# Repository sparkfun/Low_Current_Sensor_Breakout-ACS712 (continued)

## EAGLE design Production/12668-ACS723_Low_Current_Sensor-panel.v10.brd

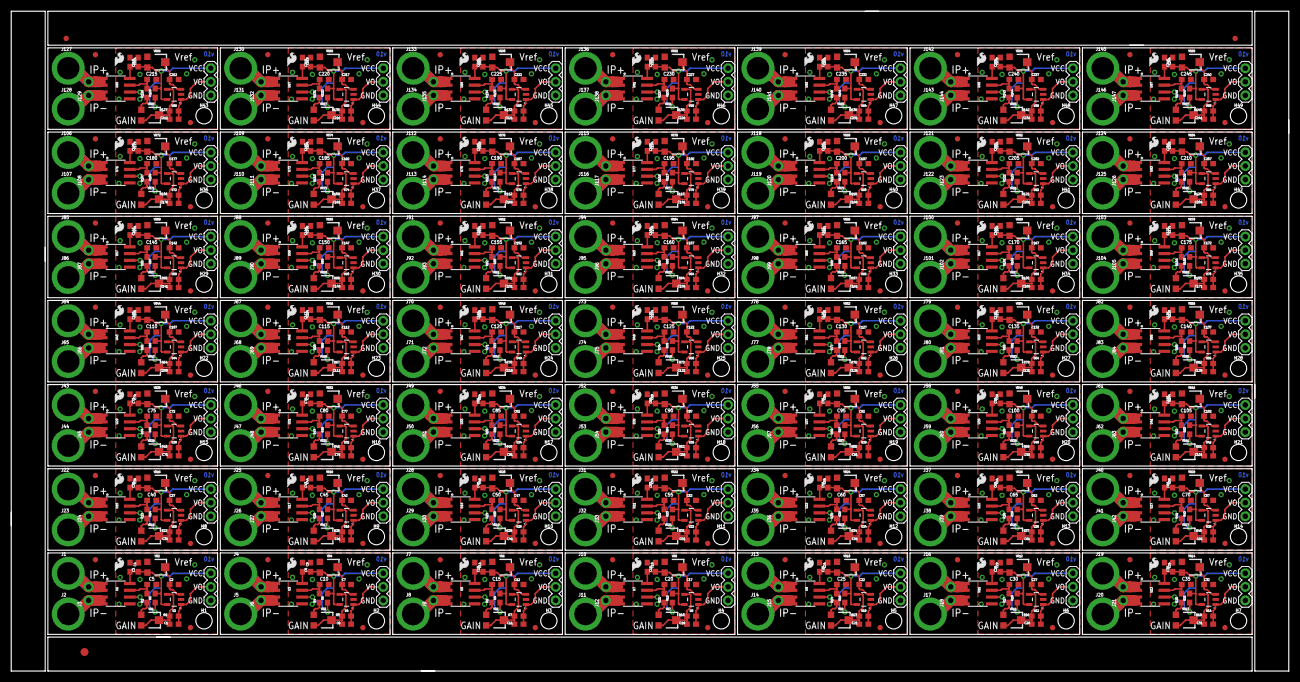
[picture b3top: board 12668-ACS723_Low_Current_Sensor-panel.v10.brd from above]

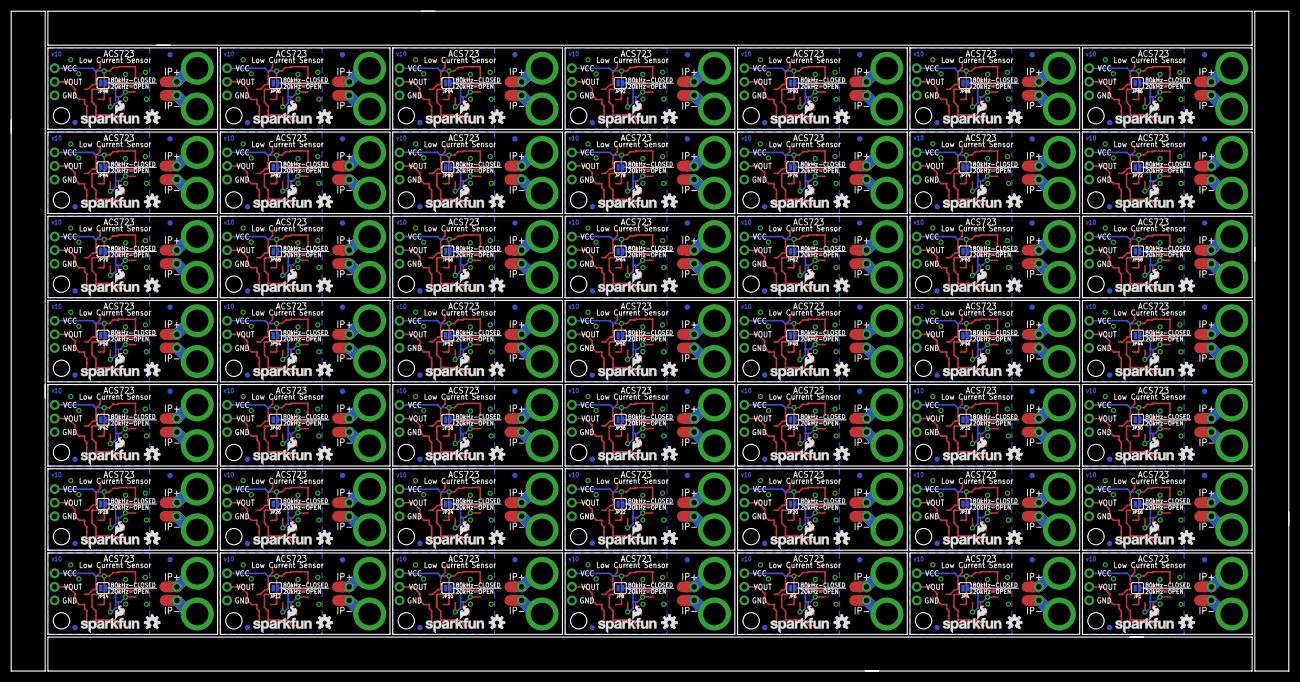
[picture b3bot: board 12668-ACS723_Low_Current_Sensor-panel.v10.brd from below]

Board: 2 copper layers, 239.0 x 123.4 mm, 1228 parts (245 on the bottom side), 490 nets.

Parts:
C1, C6, C11, C16, C21, C26, C31, C36, C41, C46, C51, C56, C61, C66, C71, C76, C81, C86, C91, C96, C101, C106, C111, C116, C121, C126, C131, C136, C141, C146, C151, C156, C161, C166, C171, C176, C181, C186, C191, C196, C201, C206, C211, C216, C221, C226, C231, C236, C241: 100pF; 0603
C2, C3, C4, C7, C8, C9, C12, C13, C14, C17, C18, C19, C22, C23, C24, C27, C28, C29, C32, C33, C34, C37, C38, C39, C42, C43, C44, C47, C48, C49, C52, C53, C54, C57, C58, C59, C62, C63, C64, C67, C68, C69, C72, C73, C74, C77, C78, C79, C82, C83, C84, C87, C88, C89, C92, C93, C94, C97, C98, C99, C102, C103, C104, C107, C108, C109, C112, C113, C114, C117, C118, C119, C122, C123, C124, C127, C128, C129, C132, C133, C134, C137, C138, C139, C142, C143, C144, C147, C148, C149, C152, C153, C154, C157, C158, C159, C162, C163, C164, C167, C168, C169, C172, C173, C174, C177, C178, C179, C182, C183, C184, C187, C188, C189, C192, C193, C194, C197, C198, C199, C202, C203, C204, C207, C208, C209, C212, C213, C214, C217, C218, C219, C222, C223, C224, C227, C228, C229, C232, C233, C234, C237, C238, C239, C242, C243, C244: 0.1uF; 0603
C5, C10, C15, C20, C25, C30, C35, C40, C45, C50, C55, C60, C65, C70, C75, C80, C85, C90, C95, C100, C105, C110, C115, C120, C125, C130, C135, C140, C145, C150, C155, C160, C165, C170, C175, C180, C185, C190, C195, C200, C205, C210, C215, C220, C225, C230, C235, C240, C245: 1nF; 0603
E$1: FIDUCIAL-1.5X3
E$7, E$8: FIDUCIAL-1X2
FD1, FD2, FD3, FD4, FD5, FD6, FD7, FD8, FD9, FD10, FD11, FD12, FD13, FD14, FD15, FD16, FD17, FD18, FD19, FD20, FD21, FD22, FD23, FD24, FD25, FD26, FD27, FD28, FD29, FD30, FD31, FD32, FD33, FD34, FD35, FD36, FD37, FD38, FD39, FD40, FD41, FD42, FD43, FD44, FD45, FD46, FD47, FD48, FD49, FD50, FD51, FD52, FD53, FD54, FD55, FD56, FD57, FD58, FD59, FD60, FD61, FD62, FD63, FD64, FD65, FD66, FD67, FD68, FD69, FD70, FD71, FD72, FD73, FD74, FD75, FD76, FD77, FD78, FD79, FD80, FD81, FD82, FD83, FD84, FD85, FD86, FD87, FD88, FD89, FD90, FD91, FD92, FD93, FD94, FD95, FD96, FD97, FD98, FD99, FD100, FD101, FD102, FD103, FD104, FD105, FD106, FD107, FD108, FD109, FD110, FD111, FD112, FD113, FD114, FD115, FD116, FD117, FD118, FD119, FD120, FD121, FD122, FD123, FD124, FD125, FD126, FD127, FD128, FD129, FD130, FD131, FD132, FD133, FD134, FD135, FD136, FD137, FD138, FD139, FD140, FD141, FD142, FD143, FD144, FD145, FD146, FD147, FD148, FD149, FD150, FD151, FD152, FD153, FD154, FD155, FD156, FD157, FD158, FD159, FD160, FD161, FD162, FD163, FD164, FD165, FD166, FD167, FD168, FD169, FD170, FD171, FD172, FD173, FD174, FD175, FD176, FD177, FD178, FD179, FD180, FD181, FD182, FD183, FD184, FD185, FD186, FD187, FD188, FD189, FD190, FD191, FD192, FD193, FD194, FD195, FD196: FIDUCIAL1X2; FIDUCIAL-1X2
H1, H2, H3, H4, H5, H6, H7, H8, H9, H10, H11, H12, H13, H14, H15, H16, H17, H18, H19, H20, H21, H22, H23, H24, H25, H26, H27, H28, H29, H30, H31, H32, H33, H34, H35, H36, H37, H38, H39, H40, H41, H42, H43, H44, H45, H46, H47, H48, H49: STAND-OFFTIGHT; STAND-OFF-TIGHT
J1, J2, J4, J5, J7, J8, J10, J11, J13, J14, J16, J17, J19, J20, J22, J23, J25, J26, J28, J29, J31, J32, J34, J35, J37, J38, J40, J41, J43, J44, J46, J47, J49, J50, J52, J53, J55, J56, J58, J59, J61, J62, J64, J65, J67, J68, J70, J71, J73, J74, J76, J77, J79, J80, J82, J83, J85, J86, J88, J89, J91, J92, J94, J95, J97, J98, J100, J101, J103, J104, J106, J107, J109, J110, J112, J113, J115, J116, J118, J119, J121, J122, J124, J125, J127, J128, J130, J131, J133, J134, J136, J137, J139, J140, J142, J143, J145, J146: SMTSO-256-ET-0.165DIA
J3, J6, J9, J12, J15, J18, J21, J24, J27, J30, J33, J36, J39, J42, J45, J48, J51, J54, J57, J60, J63, J66, J69, J72, J75, J78, J81, J84, J87, J90, J93, J96, J99, J102, J105, J108, J111, J114, J117, J120, J123, J126, J129, J132, J135, J138, J141, J144, J147: 1X02_NO_SILK
JP1, JP4, JP6, JP8, JP10, JP12, JP14, JP16, JP18, JP20, JP22, JP24, JP26, JP28, JP30, JP32, JP34, JP36, JP38, JP40, JP42, JP44, JP46, JP48, JP50, JP52, JP54, JP56, JP58, JP60, JP62, JP64, JP66, JP68, JP70, JP72, JP74, JP76, JP78, JP80, JP82, JP84, JP86, JP88, JP90, JP92, JP94, JP96, JP98: JUMPER-SMT_2_NO_SILK; SMT-JUMPER_2_NO_SILK
JP2, JP3, JP5, JP7, JP9, JP11, JP13, JP15, JP17, JP19, JP21, JP23, JP25, JP27, JP29, JP31, JP33, JP35, JP37, JP39, JP41, JP43, JP45, JP47, JP49, JP51, JP53, JP55, JP57, JP59, JP61, JP63, JP65, JP67, JP69, JP71, JP73, JP75, JP77, JP79, JP81, JP83, JP85, JP87, JP89, JP91, JP93, JP95, JP97: 1X03
LOGO1, LOGO4, LOGO7, LOGO10, LOGO13, LOGO16, LOGO19, LOGO22, LOGO25, LOGO28, LOGO31, LOGO34, LOGO37, LOGO40, LOGO43, LOGO46, LOGO49, LOGO52, LOGO55, LOGO58, LOGO61, LOGO64, LOGO67, LOGO70, LOGO73, LOGO76, LOGO79, LOGO82, LOGO85, LOGO88, LOGO91, LOGO94, LOGO97, LOGO100, LOGO103, LOGO106, LOGO109, LOGO112, LOGO115, LOGO118, LOGO121, LOGO124, LOGO127, LOGO130, LOGO133, LOGO136, LOGO139, LOGO142, LOGO145: SFE_LOGO_NAME_FLAME.1_INCH; SFE_LOGO_NAME_FLAME_.1
LOGO2, LOGO5, LOGO8, LOGO11, LOGO14, LOGO17, LOGO20, LOGO23, LOGO26, LOGO29, LOGO32, LOGO35, LOGO38, LOGO41, LOGO44, LOGO47, LOGO50, LOGO53, LOGO56, LOGO59, LOGO62, LOGO65, LOGO68, LOGO71, LOGO74, LOGO77, LOGO80, LOGO83, LOGO86, LOGO89, LOGO92, LOGO95, LOGO98, LOGO101, LOGO104, LOGO107, LOGO110, LOGO113, LOGO116, LOGO119, LOGO122, LOGO125, LOGO128, LOGO131, LOGO134, LOGO137, LOGO140, LOGO143, LOGO146: OSHW-LOGOS; OSHW-LOGO-S
LOGO3, LOGO6, LOGO9, LOGO12, LOGO15, LOGO18, LOGO21, LOGO24, LOGO27, LOGO30, LOGO33, LOGO36, LOGO39, LOGO42, LOGO45, LOGO48, LOGO51, LOGO54, LOGO57, LOGO60, LOGO63, LOGO66, LOGO69, LOGO72, LOGO75, LOGO78, LOGO81, LOGO84, LOGO87, LOGO90, LOGO93, LOGO96, LOGO99, LOGO102, LOGO105, LOGO108, LOGO111, LOGO114, LOGO117, LOGO120, LOGO123, LOGO126, LOGO129, LOGO132, LOGO135, LOGO138, LOGO141, LOGO144, LOGO147: SFE_LOGO_FLAME.1_INCH; SFE_LOGO_FLAME_.1
R1, R3, R7, R10, R13, R16, R19, R22, R25, R28, R31, R34, R37, R40, R43, R46, R49, R52, R55, R58, R61, R64, R67, R70, R73, R76, R79, R82, R85, R88, R91, R94, R97, R100, R103, R106, R109, R112, R115, R118, R121, R124, R127, R130, R133, R136, R139, R142, R145: 22k; 0603
R2, R4, R8, R11, R14, R17, R20, R23, R26, R29, R32, R35, R38, R41, R44, R47, R50, R53, R56, R59, R62, R65, R68, R71, R74, R77, R80, R83, R86, R89, R92, R95, R98, R101, R104, R107, R110, R113, R116, R119, R122, R125, R128, R131, R134, R137, R140, R143, R146: 1k; 0603
R5, R6, R9, R12, R15, R18, R21, R24, R27, R30, R33, R36, R39, R42, R45, R48, R51, R54, R57, R60, R63, R66, R69, R72, R75, R78, R81, R84, R87, R90, R93, R96, R99, R102, R105, R108, R111, R114, R117, R120, R123, R126, R129, R132, R135, R138, R141, R144, R147: 4.7k; 0603
U1, U3, U5, U7, U9, U11, U13, U15, U17, U19, U21, U23, U25, U27, U29, U31, U33, U35, U37, U39, U41, U43, U45, U47, U49, U51, U53, U55, U57, U59, U61, U63, U65, U67, U69, U71, U73, U75, U77, U79, U81, U83, U85, U87, U89, U91, U93, U95, U97: ACS723; SO08
U2, U4, U6, U8, U10, U12, U14, U16, U18, U20, U22, U24, U26, U28, U30, U32, U34, U36, U38, U40, U42, U44, U46, U48, U50, U52, U54, U56, U58, U60, U62, U64, U66, U68, U70, U72, U74, U76, U78, U80, U82, U84, U86, U88, U90, U92, U94, U96, U98: OPA344; SOT23-5
VR1, VR2, VR3, VR4, VR5, VR6, VR7, VR8, VR9, VR10, VR11, VR12, VR13, VR14, VR15, VR16, VR17, VR18, VR19, VR20, VR21, VR22, VR23, VR24, VR25, VR26, VR27, VR28, VR29, VR30, VR31, VR32, VR33, VR34, VR35, VR36, VR37, VR38, VR39, VR40, VR41, VR42, VR43, VR44, VR45, VR46, VR47, VR48, VR49, VR50, VR51, VR52, VR53, VR54, VR55, VR56, VR57, VR58, VR59, VR60, VR61, VR62, VR63, VR64, VR65, VR66, VR67, VR68, VR69, VR70, VR71, VR72, VR73, VR74, VR75, VR76, VR77, VR78, VR79, VR80, VR81, VR82, VR83, VR84, VR85, VR86, VR87, VR88, VR89, VR90, VR91, VR92, VR93, VR94, VR95, VR96, VR97, VR98: 10k; TRIMPOT-SMD-TC33X

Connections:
5V: C3.1, C4.2, JP3.1, R5.2, U1.8, U2.5, VR2.3
5V1: C8.1, C9.2, JP2.1, R6.2, U3.8, U4.5, VR4.3
5V2: C13.1, C14.2, JP5.1, R9.2, U5.8, U6.5, VR6.3
5V3: C18.1, C19.2, JP7.1, R12.2, U7.8, U8.5, VR8.3
5V4: C23.1, C24.2, JP9.1, R15.2, U9.8, U10.5, VR10.3
5V5: C28.1, C29.2, JP11.1, R18.2, U11.8, U12.5, VR12.3
5V6: C33.1, C34.2, JP13.1, R21.2, U13.8, U14.5, VR14.3
5V7: C38.1, C39.2, JP15.1, R24.2, U15.8, U16.5, VR16.3
5V8: C43.1, C44.2, JP17.1, R27.2, U17.8, U18.5, VR18.3
5V9: C48.1, C49.2, JP19.1, R30.2, U19.8, U20.5, VR20.3
5V10: C53.1, C54.2, JP21.1, R33.2, U21.8, U22.5, VR22.3
5V11: C58.1, C59.2, JP23.1, R36.2, U23.8, U24.5, VR24.3
5V12: C63.1, C64.2, JP25.1, R39.2, U25.8, U26.5, VR26.3
5V13: C68.1, C69.2, JP27.1, R42.2, U27.8, U28.5, VR28.3
5V14: C73.1, C74.2, JP29.1, R45.2, U29.8, U30.5, VR30.3
5V15: C78.1, C79.2, JP31.1, R48.2, U31.8, U32.5, VR32.3
5V16: C83.1, C84.2, JP33.1, R51.2, U33.8, U34.5, VR34.3
5V17: C88.1, C89.2, JP35.1, R54.2, U35.8, U36.5, VR36.3
5V18: C93.1, C94.2, JP37.1, R57.2, U37.8, U38.5, VR38.3
5V19: C98.1, C99.2, JP39.1, R60.2, U39.8, U40.5, VR40.3
5V20: C103.1, C104.2, JP41.1, R63.2, U41.8, U42.5, VR42.3
5V21: C108.1, C109.2, JP43.1, R66.2, U43.8, U44.5, VR44.3
5V22: C113.1, C114.2, JP45.1, R69.2, U45.8, U46.5, VR46.3
5V23: C118.1, C119.2, JP47.1, R72.2, U47.8, U48.5, VR48.3
5V24: C123.1, C124.2, JP49.1, R75.2, U49.8, U50.5, VR50.3
5V25: C128.1, C129.2, JP51.1, R78.2, U51.8, U52.5, VR52.3
5V26: C133.1, C134.2, JP53.1, R81.2, U53.8, U54.5, VR54.3
5V27: C138.1, C139.2, JP55.1, R84.2, U55.8, U56.5, VR56.3
5V28: C143.1, C144.2, JP57.1, R87.2, U57.8, U58.5, VR58.3
5V29: C148.1, C149.2, JP59.1, R90.2, U59.8, U60.5, VR60.3
5V30: C153.1, C154.2, JP61.1, R93.2, U61.8, U62.5, VR62.3
5V31: C158.1, C159.2, JP63.1, R96.2, U63.8, U64.5, VR64.3
5V32: C163.1, C164.2, JP65.1, R99.2, U65.8, U66.5, VR66.3
5V33: C168.1, C169.2, JP67.1, R102.2, U67.8, U68.5, VR68.3
5V34: C173.1, C174.2, JP69.1, R105.2, U69.8, U70.5, VR70.3
5V35: C178.1, C179.2, JP71.1, R108.2, U71.8, U72.5, VR72.3
5V36: C183.1, C184.2, JP73.1, R111.2, U73.8, U74.5, VR74.3
5V37: C188.1, C189.2, JP75.1, R114.2, U75.8, U76.5, VR76.3
5V38: C193.1, C194.2, JP77.1, R117.2, U77.8, U78.5, VR78.3
5V39: C198.1, C199.2, JP79.1, R120.2, U79.8, U80.5, VR80.3
5V40: C203.1, C204.2, JP81.1, R123.2, U81.8, U82.5, VR82.3
5V41: C208.1, C209.2, JP83.1, R126.2, U83.8, U84.5, VR84.3
5V42: C213.1, C214.2, JP85.1, R129.2, U85.8, U86.5, VR86.3
5V43: C218.1, C219.2, JP87.1, R132.2, U87.8, U88.5, VR88.3
5V44: C223.1, C224.2, JP89.1, R135.2, U89.8, U90.5, VR90.3
5V45: C228.1, C229.2, JP91.1, R138.2, U91.8, U92.5, VR92.3
5V46: C233.1, C234.2, JP93.1, R141.2, U93.8, U94.5, VR94.3
5V47: C238.1, C239.2, JP95.1, R144.2, U95.8, U96.5, VR96.3
5V48: C243.1, C244.2, JP97.1, R147.2, U97.8, U98.5, VR98.3
BW_SEL: JP1.2, R5.1, U1.6
BW_SEL1: JP4.2, R6.1, U3.6
BW_SEL2: JP6.2, R9.1, U5.6
BW_SEL3: JP8.2, R12.1, U7.6
BW_SEL4: JP10.2, R15.1, U9.6
BW_SEL5: JP12.2, R18.1, U11.6
BW_SEL6: JP14.2, R21.1, U13.6
BW_SEL7: JP16.2, R24.1, U15.6
BW_SEL8: JP18.2, R27.1, U17.6
BW_SEL9: JP20.2, R30.1, U19.6
BW_SEL10: JP22.2, R33.1, U21.6
BW_SEL11: JP24.2, R36.1, U23.6
BW_SEL12: JP26.2, R39.1, U25.6
BW_SEL13: JP28.2, R42.1, U27.6
BW_SEL14: JP30.2, R45.1, U29.6
BW_SEL15: JP32.2, R48.1, U31.6
BW_SEL16: JP34.2, R51.1, U33.6
BW_SEL17: JP36.2, R54.1, U35.6
BW_SEL18: JP38.2, R57.1, U37.6
BW_SEL19: JP40.2, R60.1, U39.6
BW_SEL20: JP42.2, R63.1, U41.6
BW_SEL21: JP44.2, R66.1, U43.6
BW_SEL22: JP46.2, R69.1, U45.6
BW_SEL23: JP48.2, R72.1, U47.6
BW_SEL24: JP50.2, R75.1, U49.6
BW_SEL25: JP52.2, R78.1, U51.6
BW_SEL26: JP54.2, R81.1, U53.6
BW_SEL27: JP56.2, R84.1, U55.6
BW_SEL28: JP58.2, R87.1, U57.6
BW_SEL29: JP60.2, R90.1, U59.6
BW_SEL30: JP62.2, R93.1, U61.6
BW_SEL31: JP64.2, R96.1, U63.6
BW_SEL32: JP66.2, R99.1, U65.6
BW_SEL33: JP68.2, R102.1, U67.6
BW_SEL34: JP70.2, R105.1, U69.6
BW_SEL35: JP72.2, R108.1, U71.6
BW_SEL36: JP74.2, R111.1, U73.6
BW_SEL37: JP76.2, R114.1, U75.6
BW_SEL38: JP78.2, R117.1, U77.6
BW_SEL39: JP80.2, R120.1, U79.6
BW_SEL40: JP82.2, R123.1, U81.6
BW_SEL41: JP84.2, R126.1, U83.6
BW_SEL42: JP86.2, R129.1, U85.6
BW_SEL43: JP88.2, R132.1, U87.6
BW_SEL44: JP90.2, R135.1, U89.6
BW_SEL45: JP92.2, R138.1, U91.6
BW_SEL46: JP94.2, R141.1, U93.6
BW_SEL47: JP96.2, R144.1, U95.6
BW_SEL48: JP98.2, R147.1, U97.6
GND: C2.2, C3.2, C4.1, C5.2, JP1.1, JP3.3, U1.5, U2.2, VR2.1
GND1: C7.2, C8.2, C9.1, C10.2, JP2.3, JP4.1, U3.5, U4.2, VR4.1
GND2: C12.2, C13.2, C14.1, C15.2, JP5.3, JP6.1, U5.5, U6.2, VR6.1
GND3: C17.2, C18.2, C19.1, C20.2, JP7.3, JP8.1, U7.5, U8.2, VR8.1
GND4: C22.2, C23.2, C24.1, C25.2, JP9.3, JP10.1, U9.5, U10.2, VR10.1
GND5: C27.2, C28.2, C29.1, C30.2, JP11.3, JP12.1, U11.5, U12.2, VR12.1
GND6: C32.2, C33.2, C34.1, C35.2, JP13.3, JP14.1, U13.5, U14.2, VR14.1
GND7: C37.2, C38.2, C39.1, C40.2, JP15.3, JP16.1, U15.5, U16.2, VR16.1
GND8: C42.2, C43.2, C44.1, C45.2, JP17.3, JP18.1, U17.5, U18.2, VR18.1
GND9: C47.2, C48.2, C49.1, C50.2, JP19.3, JP20.1, U19.5, U20.2, VR20.1
GND10: C52.2, C53.2, C54.1, C55.2, JP21.3, JP22.1, U21.5, U22.2, VR22.1
GND11: C57.2, C58.2, C59.1, C60.2, JP23.3, JP24.1, U23.5, U24.2, VR24.1
GND12: C62.2, C63.2, C64.1, C65.2, JP25.3, JP26.1, U25.5, U26.2, VR26.1
GND13: C67.2, C68.2, C69.1, C70.2, JP27.3, JP28.1, U27.5, U28.2, VR28.1
GND14: C72.2, C73.2, C74.1, C75.2, JP29.3, JP30.1, U29.5, U30.2, VR30.1
GND15: C77.2, C78.2, C79.1, C80.2, JP31.3, JP32.1, U31.5, U32.2, VR32.1
GND16: C82.2, C83.2, C84.1, C85.2, JP33.3, JP34.1, U33.5, U34.2, VR34.1
GND17: C87.2, C88.2, C89.1, C90.2, JP35.3, JP36.1, U35.5, U36.2, VR36.1
GND18: C92.2, C93.2, C94.1, C95.2, JP37.3, JP38.1, U37.5, U38.2, VR38.1
GND19: C97.2, C98.2, C99.1, C100.2, JP39.3, JP40.1, U39.5, U40.2, VR40.1
GND20: C102.2, C103.2, C104.1, C105.2, JP41.3, JP42.1, U41.5, U42.2, VR42.1
GND21: C107.2, C108.2, C109.1, C110.2, JP43.3, JP44.1, U43.5, U44.2, VR44.1
GND22: C112.2, C113.2, C114.1, C115.2, JP45.3, JP46.1, U45.5, U46.2, VR46.1
GND23: C117.2, C118.2, C119.1, C120.2, JP47.3, JP48.1, U47.5, U48.2, VR48.1
GND24: C122.2, C123.2, C124.1, C125.2, JP49.3, JP50.1, U49.5, U50.2, VR50.1
GND25: C127.2, C128.2, C129.1, C130.2, JP51.3, JP52.1, U51.5, U52.2, VR52.1
GND26: C132.2, C133.2, C134.1, C135.2, JP53.3, JP54.1, U53.5, U54.2, VR54.1
GND27: C137.2, C138.2, C139.1, C140.2, JP55.3, JP56.1, U55.5, U56.2, VR56.1
GND28: C142.2, C143.2, C144.1, C145.2, JP57.3, JP58.1, U57.5, U58.2, VR58.1
GND29: C147.2, C148.2, C149.1, C150.2, JP59.3, JP60.1, U59.5, U60.2, VR60.1
GND30: C152.2, C153.2, C154.1, C155.2, JP61.3, JP62.1, U61.5, U62.2, VR62.1
GND31: C157.2, C158.2, C159.1, C160.2, JP63.3, JP64.1, U63.5, U64.2, VR64.1
GND32: C162.2, C163.2, C164.1, C165.2, JP65.3, JP66.1, U65.5, U66.2, VR66.1
GND33: C167.2, C168.2, C169.1, C170.2, JP67.3, JP68.1, U67.5, U68.2, VR68.1
GND34: C172.2, C173.2, C174.1, C175.2, JP69.3, JP70.1, U69.5, U70.2, VR70.1
GND35: C177.2, C178.2, C179.1, C180.2, JP71.3, JP72.1, U71.5, U72.2, VR72.1
GND36: C182.2, C183.2, C184.1, C185.2, JP73.3, JP74.1, U73.5, U74.2, VR74.1
GND37: C187.2, C188.2, C189.1, C190.2, JP75.3, JP76.1, U75.5, U76.2, VR76.1
GND38: C192.2, C193.2, C194.1, C195.2, JP77.3, JP78.1, U77.5, U78.2, VR78.1
GND39: C197.2, C198.2, C199.1, C200.2, JP79.3, JP80.1, U79.5, U80.2, VR80.1
GND40: C202.2, C203.2, C204.1, C205.2, JP81.3, JP82.1, U81.5, U82.2, VR82.1
GND41: C207.2, C208.2, C209.1, C210.2, JP83.3, JP84.1, U83.5, U84.2, VR84.1
GND42: C212.2, C213.2, C214.1, C215.2, JP85.3, JP86.1, U85.5, U86.2, VR86.1
GND43: C217.2, C218.2, C219.1, C220.2, JP87.3, JP88.1, U87.5, U88.2, VR88.1
GND44: C222.2, C223.2, C224.1, C225.2, JP89.3, JP90.1, U89.5, U90.2, VR90.1
GND45: C227.2, C228.2, C229.1, C230.2, JP91.3, JP92.1, U91.5, U92.2, VR92.1
GND46: C232.2, C233.2, C234.1, C235.2, JP93.3, JP94.1, U93.5, U94.2, VR94.1
GND47: C237.2, C238.2, C239.1, C240.2, JP95.3, JP96.1, U95.5, U96.2, VR96.1
GND48: C242.2, C243.2, C244.1, C245.2, JP97.3, JP98.1, U97.5, U98.2, VR98.1
IP+: J1.P$1, J3.2, U1.1, U1.2
IP+1: J4.P$1, J6.2, U3.1, U3.2
IP+2: J7.P$1, J9.2, U5.1, U5.2
IP+3: J10.P$1, J12.2, U7.1, U7.2
IP+4: J13.P$1, J15.2, U9.1, U9.2
IP+5: J16.P$1, J18.2, U11.1, U11.2
IP+6: J19.P$1, J21.2, U13.1, U13.2
IP+7: J22.P$1, J24.2, U15.1, U15.2
IP+8: J25.P$1, J27.2, U17.1, U17.2
IP+9: J28.P$1, J30.2, U19.1, U19.2
IP+10: J31.P$1, J33.2, U21.1, U21.2
IP+11: J34.P$1, J36.2, U23.1, U23.2
IP+12: J37.P$1, J39.2, U25.1, U25.2
IP+13: J40.P$1, J42.2, U27.1, U27.2
IP+14: J43.P$1, J45.2, U29.1, U29.2
IP+15: J46.P$1, J48.2, U31.1, U31.2
IP+16: J49.P$1, J51.2, U33.1, U33.2
IP+17: J52.P$1, J54.2, U35.1, U35.2
IP+18: J55.P$1, J57.2, U37.1, U37.2
IP+19: J58.P$1, J60.2, U39.1, U39.2
IP+20: J61.P$1, J63.2, U41.1, U41.2
IP+21: J64.P$1, J66.2, U43.1, U43.2
IP+22: J67.P$1, J69.2, U45.1, U45.2
IP+23: J70.P$1, J72.2, U47.1, U47.2
IP+24: J73.P$1, J75.2, U49.1, U49.2
IP+25: J76.P$1, J78.2, U51.1, U51.2
IP+26: J79.P$1, J81.2, U53.1, U53.2
IP+27: J82.P$1, J84.2, U55.1, U55.2
IP+28: J85.P$1, J87.2, U57.1, U57.2
IP+29: J88.P$1, J90.2, U59.1, U59.2
IP+30: J91.P$1, J93.2, U61.1, U61.2
IP+31: J94.P$1, J96.2, U63.1, U63.2
IP+32: J97.P$1, J99.2, U65.1, U65.2
IP+33: J100.P$1, J102.2, U67.1, U67.2
IP+34: J103.P$1, J105.2, U69.1, U69.2
IP+35: J106.P$1, J108.2, U71.1, U71.2
IP+36: J109.P$1, J111.2, U73.1, U73.2
IP+37: J112.P$1, J114.2, U75.1, U75.2
IP+38: J115.P$1, J117.2, U77.1, U77.2
IP+39: J118.P$1, J120.2, U79.1, U79.2
IP+40: J121.P$1, J123.2, U81.1, U81.2
IP+41: J124.P$1, J126.2, U83.1, U83.2
IP+42: J127.P$1, J129.2, U85.1, U85.2
IP+43: J130.P$1, J132.2, U87.1, U87.2
IP+44: J133.P$1, J135.2, U89.1, U89.2
IP+45: J136.P$1, J138.2, U91.1, U91.2
IP+46: J139.P$1, J141.2, U93.1, U93.2
IP+47: J142.P$1, J144.2, U95.1, U95.2
IP+48: J145.P$1, J147.2, U97.1, U97.2
IP-: J2.P$1, J3.1, U1.3, U1.4
IP-1: J5.P$1, J6.1, U3.3, U3.4
IP-2: J8.P$1, J9.1, U5.3, U5.4
IP-3: J11.P$1, J12.1, U7.3, U7.4
IP-4: J14.P$1, J15.1, U9.3, U9.4
IP-5: J17.P$1, J18.1, U11.3, U11.4
IP-6: J20.P$1, J21.1, U13.3, U13.4
IP-7: J23.P$1, J24.1, U15.3, U15.4
IP-8: J26.P$1, J27.1, U17.3, U17.4
IP-9: J29.P$1, J30.1, U19.3, U19.4
IP-10: J32.P$1, J33.1, U21.3, U21.4
IP-11: J35.P$1, J36.1, U23.3, U23.4
IP-12: J38.P$1, J39.1, U25.3, U25.4
IP-13: J41.P$1, J42.1, U27.3, U27.4
IP-14: J44.P$1, J45.1, U29.3, U29.4
IP-15: J47.P$1, J48.1, U31.3, U31.4
IP-16: J50.P$1, J51.1, U33.3, U33.4
IP-17: J53.P$1, J54.1, U35.3, U35.4
IP-18: J56.P$1, J57.1, U37.3, U37.4
IP-19: J59.P$1, J60.1, U39.3, U39.4
IP-20: J62.P$1, J63.1, U41.3, U41.4
IP-21: J65.P$1, J66.1, U43.3, U43.4
IP-22: J68.P$1, J69.1, U45.3, U45.4
IP-23: J71.P$1, J72.1, U47.3, U47.4
IP-24: J74.P$1, J75.1, U49.3, U49.4
IP-25: J77.P$1, J78.1, U51.3, U51.4
IP-26: J80.P$1, J81.1, U53.3, U53.4
IP-27: J83.P$1, J84.1, U55.3, U55.4
IP-28: J86.P$1, J87.1, U57.3, U57.4
IP-29: J89.P$1, J90.1, U59.3, U59.4
IP-30: J92.P$1, J93.1, U61.3, U61.4
IP-31: J95.P$1, J96.1, U63.3, U63.4
IP-32: J98.P$1, J99.1, U65.3, U65.4
IP-33: J101.P$1, J102.1, U67.3, U67.4
IP-34: J104.P$1, J105.1, U69.3, U69.4
IP-35: J107.P$1, J108.1, U71.3, U71.4
IP-36: J110.P$1, J111.1, U73.3, U73.4
IP-37: J113.P$1, J114.1, U75.3, U75.4
IP-38: J116.P$1, J117.1, U77.3, U77.4
IP-39: J119.P$1, J120.1, U79.3, U79.4
IP-40: J122.P$1, J123.1, U81.3, U81.4
IP-41: J125.P$1, J126.1, U83.3, U83.4
IP-42: J128.P$1, J129.1, U85.3, U85.4
IP-43: J131.P$1, J132.1, U87.3, U87.4
IP-44: J134.P$1, J135.1, U89.3, U89.4
IP-45: J137.P$1, J138.1, U91.3, U91.4
IP-46: J140.P$1, J141.1, U93.3, U93.4
IP-47: J143.P$1, J144.1, U95.3, U95.4
IP-48: J146.P$1, J147.1, U97.3, U97.4
unnamed: R4.1, VR3.1
unnamed: C6.2, R3.2, U4.4, VR3.2, VR3.3
unnamed: C7.1, U4.3, VR4.2
unnamed: R2.1, VR1.1
unnamed: C1.2, R1.2, U2.4, VR1.2, VR1.3
unnamed: C2.1, U2.3, VR2.2
unnamed: R8.1, VR5.1
unnamed: C11.2, R7.2, U6.4, VR5.2, VR5.3
unnamed: C12.1, U6.3, VR6.2
unnamed: R11.1, VR7.1
unnamed: C16.2, R10.2, U8.4, VR7.2, VR7.3
unnamed: C17.1, U8.3, VR8.2
unnamed: R14.1, VR9.1
unnamed: C21.2, R13.2, U10.4, VR9.2, VR9.3
unnamed: C22.1, U10.3, VR10.2
unnamed: R17.1, VR11.1
unnamed: C26.2, R16.2, U12.4, VR11.2, VR11.3
unnamed: C27.1, U12.3, VR12.2
unnamed: R20.1, VR13.1
unnamed: C31.2, R19.2, U14.4, VR13.2, VR13.3
unnamed: C32.1, U14.3, VR14.2
unnamed: R23.1, VR15.1
unnamed: C36.2, R22.2, U16.4, VR15.2, VR15.3
unnamed: C37.1, U16.3, VR16.2
unnamed: R26.1, VR17.1
unnamed: C41.2, R25.2, U18.4, VR17.2, VR17.3
unnamed: C42.1, U18.3, VR18.2
unnamed: R29.1, VR19.1
unnamed: C46.2, R28.2, U20.4, VR19.2, VR19.3
unnamed: C47.1, U20.3, VR20.2
unnamed: R32.1, VR21.1
unnamed: C51.2, R31.2, U22.4, VR21.2, VR21.3
unnamed: C52.1, U22.3, VR22.2
unnamed: R35.1, VR23.1
unnamed: C56.2, R34.2, U24.4, VR23.2, VR23.3
unnamed: C57.1, U24.3, VR24.2
unnamed: R38.1, VR25.1
unnamed: C61.2, R37.2, U26.4, VR25.2, VR25.3
unnamed: C62.1, U26.3, VR26.2
unnamed: R41.1, VR27.1
unnamed: C66.2, R40.2, U28.4, VR27.2, VR27.3
unnamed: C67.1, U28.3, VR28.2
unnamed: R44.1, VR29.1
unnamed: C71.2, R43.2, U30.4, VR29.2, VR29.3
unnamed: C72.1, U30.3, VR30.2
unnamed: R47.1, VR31.1
unnamed: C76.2, R46.2, U32.4, VR31.2, VR31.3
unnamed: C77.1, U32.3, VR32.2
unnamed: R50.1, VR33.1
unnamed: C81.2, R49.2, U34.4, VR33.2, VR33.3
unnamed: C82.1, U34.3, VR34.2
unnamed: R53.1, VR35.1
unnamed: C86.2, R52.2, U36.4, VR35.2, VR35.3
unnamed: C87.1, U36.3, VR36.2
unnamed: R56.1, VR37.1
unnamed: C91.2, R55.2, U38.4, VR37.2, VR37.3
unnamed: C92.1, U38.3, VR38.2
unnamed: R59.1, VR39.1
unnamed: C96.2, R58.2, U40.4, VR39.2, VR39.3
unnamed: C97.1, U40.3, VR40.2
unnamed: R62.1, VR41.1
unnamed: C101.2, R61.2, U42.4, VR41.2, VR41.3
unnamed: C102.1, U42.3, VR42.2
unnamed: R65.1, VR43.1
unnamed: C106.2, R64.2, U44.4, VR43.2, VR43.3
unnamed: C107.1, U44.3, VR44.2
unnamed: R68.1, VR45.1
unnamed: C111.2, R67.2, U46.4, VR45.2, VR45.3
unnamed: C112.1, U46.3, VR46.2
unnamed: R71.1, VR47.1
unnamed: C116.2, R70.2, U48.4, VR47.2, VR47.3
unnamed: C117.1, U48.3, VR48.2
unnamed: R74.1, VR49.1
unnamed: C121.2, R73.2, U50.4, VR49.2, VR49.3
unnamed: C122.1, U50.3, VR50.2
unnamed: R77.1, VR51.1
unnamed: C126.2, R76.2, U52.4, VR51.2, VR51.3
unnamed: C127.1, U52.3, VR52.2
unnamed: R80.1, VR53.1
unnamed: C131.2, R79.2, U54.4, VR53.2, VR53.3
unnamed: C132.1, U54.3, VR54.2
unnamed: R83.1, VR55.1
unnamed: C136.2, R82.2, U56.4, VR55.2, VR55.3
unnamed: C137.1, U56.3, VR56.2
unnamed: R86.1, VR57.1
unnamed: C141.2, R85.2, U58.4, VR57.2, VR57.3
unnamed: C142.1, U58.3, VR58.2
unnamed: R89.1, VR59.1
unnamed: C146.2, R88.2, U60.4, VR59.2, VR59.3
unnamed: C147.1, U60.3, VR60.2
unnamed: R92.1, VR61.1
unnamed: C151.2, R91.2, U62.4, VR61.2, VR61.3
unnamed: C152.1, U62.3, VR62.2
unnamed: R95.1, VR63.1
unnamed: C156.2, R94.2, U64.4, VR63.2, VR63.3
unnamed: C157.1, U64.3, VR64.2
unnamed: R98.1, VR65.1
unnamed: C161.2, R97.2, U66.4, VR65.2, VR65.3
unnamed: C162.1, U66.3, VR66.2
unnamed: R101.1, VR67.1
unnamed: C166.2, R100.2, U68.4, VR67.2, VR67.3
unnamed: C167.1, U68.3, VR68.2
unnamed: R104.1, VR69.1
unnamed: C171.2, R103.2, U70.4, VR69.2, VR69.3
unnamed: C172.1, U70.3, VR70.2
unnamed: R107.1, VR71.1
unnamed: C176.2, R106.2, U72.4, VR71.2, VR71.3
unnamed: C177.1, U72.3, VR72.2
unnamed: R110.1, VR73.1
unnamed: C181.2, R109.2, U74.4, VR73.2, VR73.3
unnamed: C182.1, U74.3, VR74.2
unnamed: R113.1, VR75.1
unnamed: C186.2, R112.2, U76.4, VR75.2, VR75.3
unnamed: C187.1, U76.3, VR76.2
unnamed: R116.1, VR77.1
unnamed: C191.2, R115.2, U78.4, VR77.2, VR77.3
unnamed: C192.1, U78.3, VR78.2
unnamed: R119.1, VR79.1
unnamed: C196.2, R118.2, U80.4, VR79.2, VR79.3
unnamed: C197.1, U80.3, VR80.2
unnamed: R122.1, VR81.1
unnamed: C201.2, R121.2, U82.4, VR81.2, VR81.3
unnamed: C202.1, U82.3, VR82.2
unnamed: R125.1, VR83.1
unnamed: C206.2, R124.2, U84.4, VR83.2, VR83.3
unnamed: C207.1, U84.3, VR84.2
unnamed: R128.1, VR85.1
unnamed: C211.2, R127.2, U86.4, VR85.2, VR85.3
unnamed: C212.1, U86.3, VR86.2
unnamed: R131.1, VR87.1
unnamed: C216.2, R130.2, U88.4, VR87.2, VR87.3
unnamed: C217.1, U88.3, VR88.2
unnamed: R134.1, VR89.1
unnamed: C221.2, R133.2, U90.4, VR89.2, VR89.3
unnamed: C222.1, U90.3, VR90.2
unnamed: R137.1, VR91.1
unnamed: C226.2, R136.2, U92.4, VR91.2, VR91.3
unnamed: C227.1, U92.3, VR92.2
unnamed: R140.1, VR93.1
unnamed: C231.2, R139.2, U94.4, VR93.2, VR93.3
unnamed: C232.1, U94.3, VR94.2
unnamed: R143.1, VR95.1
unnamed: C236.2, R142.2, U96.4, VR95.2, VR95.3
unnamed: C237.1, U96.3, VR96.2
unnamed: R146.1, VR97.1
unnamed: C241.2, R145.2, U98.4, VR97.2, VR97.3
unnamed: C242.1, U98.3, VR98.2
VIOUT: C5.1, R2.2, U1.7
VIOUT1: C10.1, R4.2, U3.7
VIOUT2: C15.1, R8.2, U5.7
VIOUT3: C20.1, R11.2, U7.7
VIOUT4: C25.1, R14.2, U9.7
VIOUT5: C30.1, R17.2, U11.7
VIOUT6: C35.1, R20.2, U13.7
VIOUT7: C40.1, R23.2, U15.7
VIOUT8: C45.1, R26.2, U17.7
VIOUT9: C50.1, R29.2, U19.7
VIOUT10: C55.1, R32.2, U21.7
VIOUT11: C60.1, R35.2, U23.7
VIOUT12: C65.1, R38.2, U25.7
VIOUT13: C70.1, R41.2, U27.7
VIOUT14: C75.1, R44.2, U29.7
VIOUT15: C80.1, R47.2, U31.7
VIOUT16: C85.1, R50.2, U33.7
VIOUT17: C90.1, R53.2, U35.7
VIOUT18: C95.1, R56.2, U37.7
VIOUT19: C100.1, R59.2, U39.7
VIOUT20: C105.1, R62.2, U41.7
VIOUT21: C110.1, R65.2, U43.7
VIOUT22: C115.1, R68.2, U45.7
VIOUT23: C120.1, R71.2, U47.7
VIOUT24: C125.1, R74.2, U49.7
VIOUT25: C130.1, R77.2, U51.7
VIOUT26: C135.1, R80.2, U53.7
VIOUT27: C140.1, R83.2, U55.7
VIOUT28: C145.1, R86.2, U57.7
VIOUT29: C150.1, R89.2, U59.7
VIOUT30: C155.1, R92.2, U61.7
VIOUT31: C160.1, R95.2, U63.7
VIOUT32: C165.1, R98.2, U65.7
VIOUT33: C170.1, R101.2, U67.7
VIOUT34: C175.1, R104.2, U69.7
VIOUT35: C180.1, R107.2, U71.7
VIOUT36: C185.1, R110.2, U73.7
VIOUT37: C190.1, R113.2, U75.7
VIOUT38: C195.1, R116.2, U77.7
VIOUT39: C200.1, R119.2, U79.7
VIOUT40: C205.1, R122.2, U81.7
VIOUT41: C210.1, R125.2, U83.7
VIOUT42: C215.1, R128.2, U85.7
VIOUT43: C220.1, R131.2, U87.7
VIOUT44: C225.1, R134.2, U89.7
VIOUT45: C230.1, R137.2, U91.7
VIOUT46: C235.1, R140.2, U93.7
VIOUT47: C240.1, R143.2, U95.7
VIOUT48: C245.1, R146.2, U97.7
VO: C1.1, JP3.2, R1.1, U2.1
VO1: C6.1, JP2.2, R3.1, U4.1
VO2: C11.1, JP5.2, R7.1, U6.1
VO3: C16.1, JP7.2, R10.1, U8.1
VO4: C21.1, JP9.2, R13.1, U10.1
VO5: C26.1, JP11.2, R16.1, U12.1
VO6: C31.1, JP13.2, R19.1, U14.1
VO7: C36.1, JP15.2, R22.1, U16.1
VO8: C41.1, JP17.2, R25.1, U18.1
VO9: C46.1, JP19.2, R28.1, U20.1
VO10: C51.1, JP21.2, R31.1, U22.1
VO11: C56.1, JP23.2, R34.1, U24.1
VO12: C61.1, JP25.2, R37.1, U26.1
VO13: C66.1, JP27.2, R40.1, U28.1
VO14: C71.1, JP29.2, R43.1, U30.1
VO15: C76.1, JP31.2, R46.1, U32.1
VO16: C81.1, JP33.2, R49.1, U34.1
VO17: C86.1, JP35.2, R52.1, U36.1
VO18: C91.1, JP37.2, R55.1, U38.1
VO19: C96.1, JP39.2, R58.1, U40.1
VO20: C101.1, JP41.2, R61.1, U42.1
VO21: C106.1, JP43.2, R64.1, U44.1
VO22: C111.1, JP45.2, R67.1, U46.1
VO23: C116.1, JP47.2, R70.1, U48.1
VO24: C121.1, JP49.2, R73.1, U50.1
VO25: C126.1, JP51.2, R76.1, U52.1
VO26: C131.1, JP53.2, R79.1, U54.1
VO27: C136.1, JP55.2, R82.1, U56.1
VO28: C141.1, JP57.2, R85.1, U58.1
VO29: C146.1, JP59.2, R88.1, U60.1
VO30: C151.1, JP61.2, R91.1, U62.1
VO31: C156.1, JP63.2, R94.1, U64.1
VO32: C161.1, JP65.2, R97.1, U66.1
VO33: C166.1, JP67.2, R100.1, U68.1
VO34: C171.1, JP69.2, R103.1, U70.1
VO35: C176.1, JP71.2, R106.1, U72.1
VO36: C181.1, JP73.2, R109.1, U74.1
VO37: C186.1, JP75.2, R112.1, U76.1
VO38: C191.1, JP77.2, R115.1, U78.1
VO39: C196.1, JP79.2, R118.1, U80.1
VO40: C201.1, JP81.2, R121.1, U82.1
VO41: C206.1, JP83.2, R124.1, U84.1
VO42: C211.1, JP85.2, R127.1, U86.1
VO43: C216.1, JP87.2, R130.1, U88.1
VO44: C221.1, JP89.2, R133.1, U90.1
VO45: C226.1, JP91.2, R136.1, U92.1
VO46: C231.1, JP93.2, R139.1, U94.1
VO47: C236.1, JP95.2, R142.1, U96.1
VO48: C241.1, JP97.2, R145.1, U98.1
